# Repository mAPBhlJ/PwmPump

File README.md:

Modern heating (water)pumps can be controlled using PWM, this allows for fine-grained remote control regarding the pump speed, for integration into home automation software.

# Pump

This project is designed to work work with the following pump(s):

- Grundfos UPM3-Hybrid

Other (Grundfos) pumps may be compatible with little (software) changes, other brands may require hardware changes as well. Pull requests (even if it's just to update the list, are welcome)

# Hardware

Besides the pump, the project is built around the following hardware:

- ESP32 development board with USB (SKU: 001443)
- High speed logic level converter (SKU: 000275)
- 'Mini Superseal' cable (SKU: 6057076)
- 5V power supply for dev board
- Adapter PCB from this project*

*The PCB is optional, you can build the same layout on a breadboard or perfboard. This project is created in LibrePCB but all files required for production are included.

The ESP32 is more capable as the ESP8266 but also has built-in WiFi, allowing more room for future functionalities.
For safety and simpler schematics, 230V to 5V is done via a regular power adapter commonly used for phones.

## PCB

The PCB is  designed in KiCad, source files are available in the 'pcb/PwmPump' folder.
If you do not want to change anything but just order the PCB's from any supplier, you can use the files in 'pcb/Fabrication'.

# Software

## Features
TODO:
- [ ] Control pump speed via PWM
- [ ] Read pump speed via return signal
- [ ] External temperature sensor readout
- [ ] Easy setup via WiFi accesspoint
- [ ] Integration with Home Assistant / MQTT?
- [ ] External relay outputs for toggling zones

# Documentation / troubleshooting

Below there's some additional documentation used for troubleshooting/explanation, most is taken off the original Grundfoss manual (see sources below).

## Connections

Using the 'Mini superseal' connector, make sure the connections are as following:

## Settings

For PWM operation, the first LED should be red and the second LED should be yellow and LED 3/4/5 will show the current speed.

If the first/second LED are incorrect, refer to the steps below to change the mode of the UPM3.

## PWM Signal

From the original [Grundfoss PWM Documentation](files/Grundfosliterature-5439390.pdf):

From the documentation we can conclude that the PWM signal of the ESP32 should have the following characteristics:

- 4-24V (We will use the USB voltage, 5V through a logic level shifter)
- 100-4000 Hz range

## Feedback (return) signal

The feedback signal is 75 Hz (13 milliseconds)

If the signal is on for 95% of the time, the pump is off, anywhere within 0-70% is 0-70w or 0-140w consumption, any other percentage above 70% is an error situation, see table.

# External sources

Original project start(s) in Dutch on Tweakers.net:
- https://gathering.tweakers.net/forum/list_messages/2053330
- https://gathering.tweakers.net/forum/list_messages/1843779
- https://gathering.tweakers.net/forum/list_messages/2209694

Project by a Russian with similar purpose (however using Arduino Nano with Bluetooth):
- https://www.youtube.com/watch?v=SqCPmwxaVGU
- https://drive.google.com/drive/folders/1dqcaZ_V3Xg_vkUAnDyD56ceDHpH-dQGv

# License
 GNU Affero General Public License v3.0

 Conditions
    ⓘ Disclose source
    ⓘ License and copyright notice
    ⓘ Network use is distribution
    ⓘ Same license
    ⓘ State changes 

You should have received a copy of the GNU General Public License along with this program.  If not, see <https://www.gnu.org/licenses/>.

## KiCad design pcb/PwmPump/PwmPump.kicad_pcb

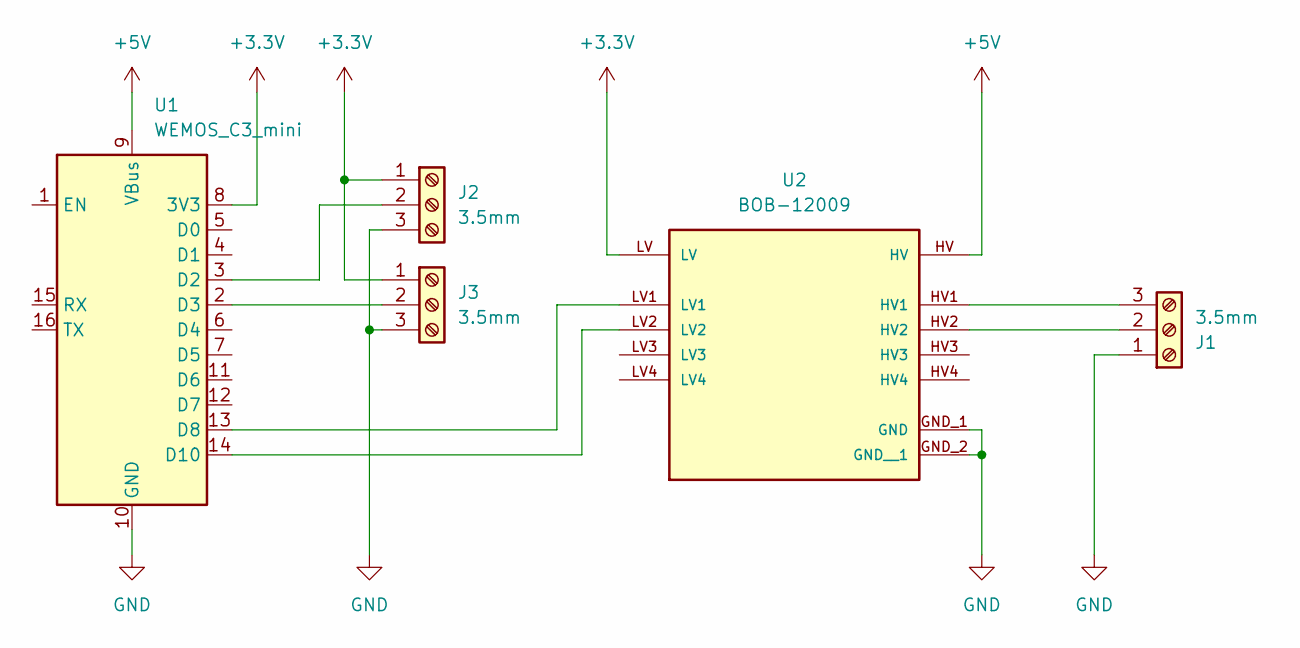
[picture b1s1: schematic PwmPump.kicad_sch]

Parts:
J1, J2, J3: 3.5mm; ScrewTerminal_1x03_P3.5mm_Horizontal_Black
U1: WEMOS_C3_mini
U2: BOB-12009; CONV_BOB-12009; PARTREV 01

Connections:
+3.3V: J2.1, J3.1, U1.8 (3V3), U2.LV
+5V: U1.9 (VBus), U2.HV
GND: J1.1, J2.3, J3.3, U1.10 (GND), U2.GND_1 (GND), U2.GND_2 (GND__1)
unnamed: J1.2, U2.HV2
unnamed: J1.3, U2.HV1
unnamed: J2.2, U1.3 (D2)
unnamed: J3.2, U1.2 (D3)
unnamed: U1.13 (D8), U2.LV1
unnamed: U1.14 (D10), U2.LV2

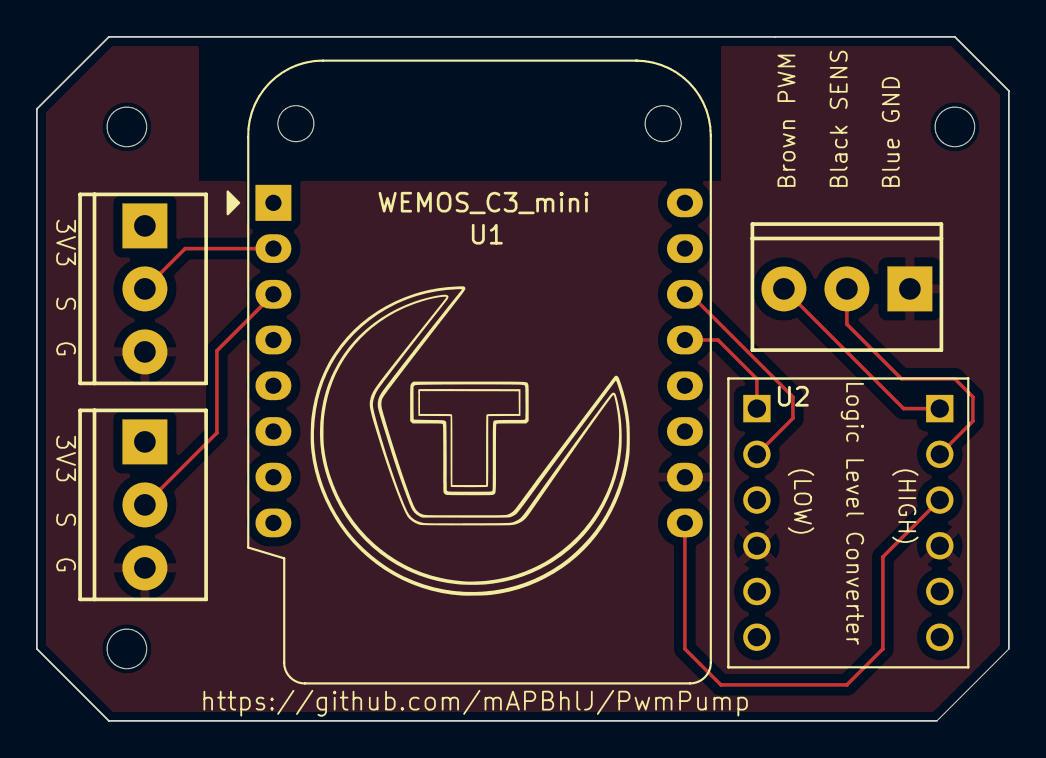
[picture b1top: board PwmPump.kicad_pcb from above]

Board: 2 copper layers, 54.0 x 38.0 mm, 5 parts (0 on the bottom side), 9 nets.

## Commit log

2026-03-07 Updated: Added 2nd analog input
